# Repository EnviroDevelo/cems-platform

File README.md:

# CEMS Core Platform firmware

Shared firmware platform for the CEMS Supervisor instrument family (STM32H5, FreeRTOS,
lwIP, Riverdi EVE4). It runs the translated Valve Manager / Multiplexor program as a
PLC-style scan and provides the services around it.

- `docs/APP_INTEGRATION.md`: handover for the VM/MUX application build (what to supply, rules, open items)
- `docs/PLATFORM.md`: structure, task priorities, the scan contract, integration rules, decisions needed
- `docs/CUBEMX_SETUP.md`: bringing it up on the STM32H573I-DK in STM32CubeIDE
- `docs/MEMORY.md`: flash and RAM used by each module against the chip's limits (kept current)

## Host builds (Linux/macOS/WSL, gcc)

```
make test      # unit tests (with both FRAM memory maps; includes 400 random power cuts on the log)
make sim       # PC simulation of the demo application
make netsim    # the platform on real sockets: Modbus TCP on 1502, web on https://127.0.0.1:8443/
               # (FRAM and log flash are files: netsim_fram.bin, netsim_nor.bin)
               # (type "remote" / "local" on stdin to act as the touchscreen)
make rtos      # the real FreeRTOS task layer on the FreeRTOS POSIX port (needs EXT=path with FreeRTOS-Kernel)
make target    # compile-check for STM32H5 with arm-none-eabi-gcc (needs EXT, see port/stm32h5/check.mk)
tools/check_target.sh   # compile and link the target in six configurations; updates docs/MEMORY.md
```

Integration tests (with netsim built): `python3 tests/integration/net_test.py` (needs
pymodbus on PYTHONPATH), `python3 tests/integration/fw_test.py` (firmware update and
rollback), `python3 tests/integration/mail_test.py` (alarm email against a test mail
server; needs openssl), `python3 tests/integration/clock_test.py` (clock and SNTP), `python3 tests/integration/serial_test.py` (serial number tokens; needs Python cryptography),
`python3 tests/integration/soak_test.py [minutes]` (soak with memory and socket watch; needs pymodbus) and `python3 tests/integration/web_ui_test.py` (needs Python Playwright and
Chromium).

The application contract (`plat_app_t`) now includes `fw_safe` (may a firmware restart
happen now?) and `alarms`; see `app_demo/`.

Firmware update files: `tools/mkfwimage.py build.bin cems-x.y.z.cfw --version x.y.z`
(add `--key <pem>` to sign; key set-up in `docs/CUBEMX_SETUP.md` 3d).

Touchscreen previews: `UI_DUMP=build/ui ./build/tests` writes each screen's EVE command
list, and `python3 tools/eve_preview.py build/ui/*.eve` renders them to PNG (needs
Pillow). Current screens: `docs/ui/`.

The product build is the STM32CubeIDE project. These host builds are for testing
outside the IDE.
Third-party licences: `docs/THIRD_PARTY.md`. Schematic list and bring-up checks: `docs/HARDWARE.md`.
Screen colours, states, quality marks and wording for every product: `docs/UI_CONVENTIONS.md`.
First run of the touchscreen on hardware, step by step: `docs/HMI_BENCH_TEST.md` (System > Display test on the screen).
Operator manual for the touchscreen: `docs/OPERATOR_MANUAL.md`.

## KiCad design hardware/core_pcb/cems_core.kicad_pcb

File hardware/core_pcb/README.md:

# Core PCB (KiCad 7)

The CEMS core board schematic, rev 0.1 (draft for review). Design spec, pin map and
decisions: [`docs/CORE_PCB.md`](../../docs/CORE_PCB.md).

| File | What |
|---|---|
| `cems_core.pdf` | All sheets, for review without KiCad |
| `cems_core.kicad_pro`, `cems_core.kicad_sch` | KiCad project and root sheet |
| `power`, `mcu`, `eth_client`, `eth_io`, `periph`, `io_dig`, `io_pwr`, `io_ana` `.kicad_sch` | The eight sheets (rev 0.2: 434 parts, 314 nets) |
| `cems_core.kicad_sym`, `sym-lib-table` | Project symbols (the MB85RC1MT FRAM) |
| `bom.csv` | Grouped bill of materials |
| `tools/design.py` | **The circuit, as data: edit this, not the sheets** |
| `tools/gen_schematic.py` | Writes the sheets and `bom.csv` from `design.py` |
| `cems_core.kicad_pcb`, `cems_core.kicad_dru`, `cems_core.pretty/` | Layout start (block plan, unrouted), isolation rules, project footprints. CORE_PCB.md 10a |
| `tools/gen_pcb.py`, `tools/gen_footprints.py` | Write the board and the project footprints from `design.py` |
| `tools/project_symbols.py` | Pin tables of the six I/O chips missing from KiCad (all CHECK) |
| `tools/check_netlist.py` | Checks KiCad's exported netlist against `design.py`, pin by pin |
| `tools/build.sh` | Runs all three and exports the PDF |

Needs KiCad 7 (`kicad-cli` and its symbol libraries; Ubuntu: `apt install kicad
kicad-symbols kicad-footprints`) and `pip install kiutils`. Footprints are the KiCad 7
library names, so the netlist imports straight into Pcbnew for layout.

Once layout starts, the schematic may be tidied by hand in KiCad (wires in place of
labels). From then on it is the source, and `design.py` is kept only as a record.

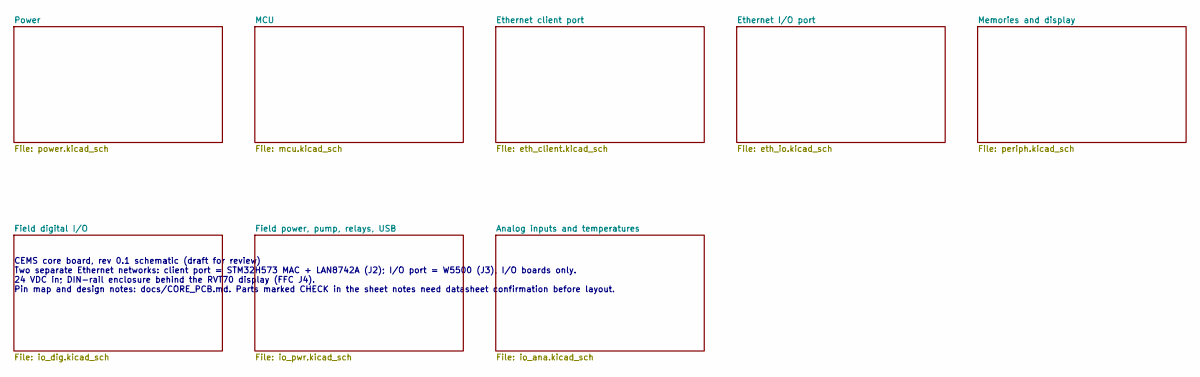
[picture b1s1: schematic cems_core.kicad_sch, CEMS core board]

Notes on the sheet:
CEMS core board, rev 0.1 schematic (draft for review) Two separate Ethernet networks: client port = STM32H573 MAC + LAN8742A (J2); I/O port = W5500 (J3), I/O boards only. 24 VDC in; DIN-rail enclosure behind the RVT70 display (FFC J4). Pin map and design notes: docs/CORE_PCB.md. Parts marked CHECK 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

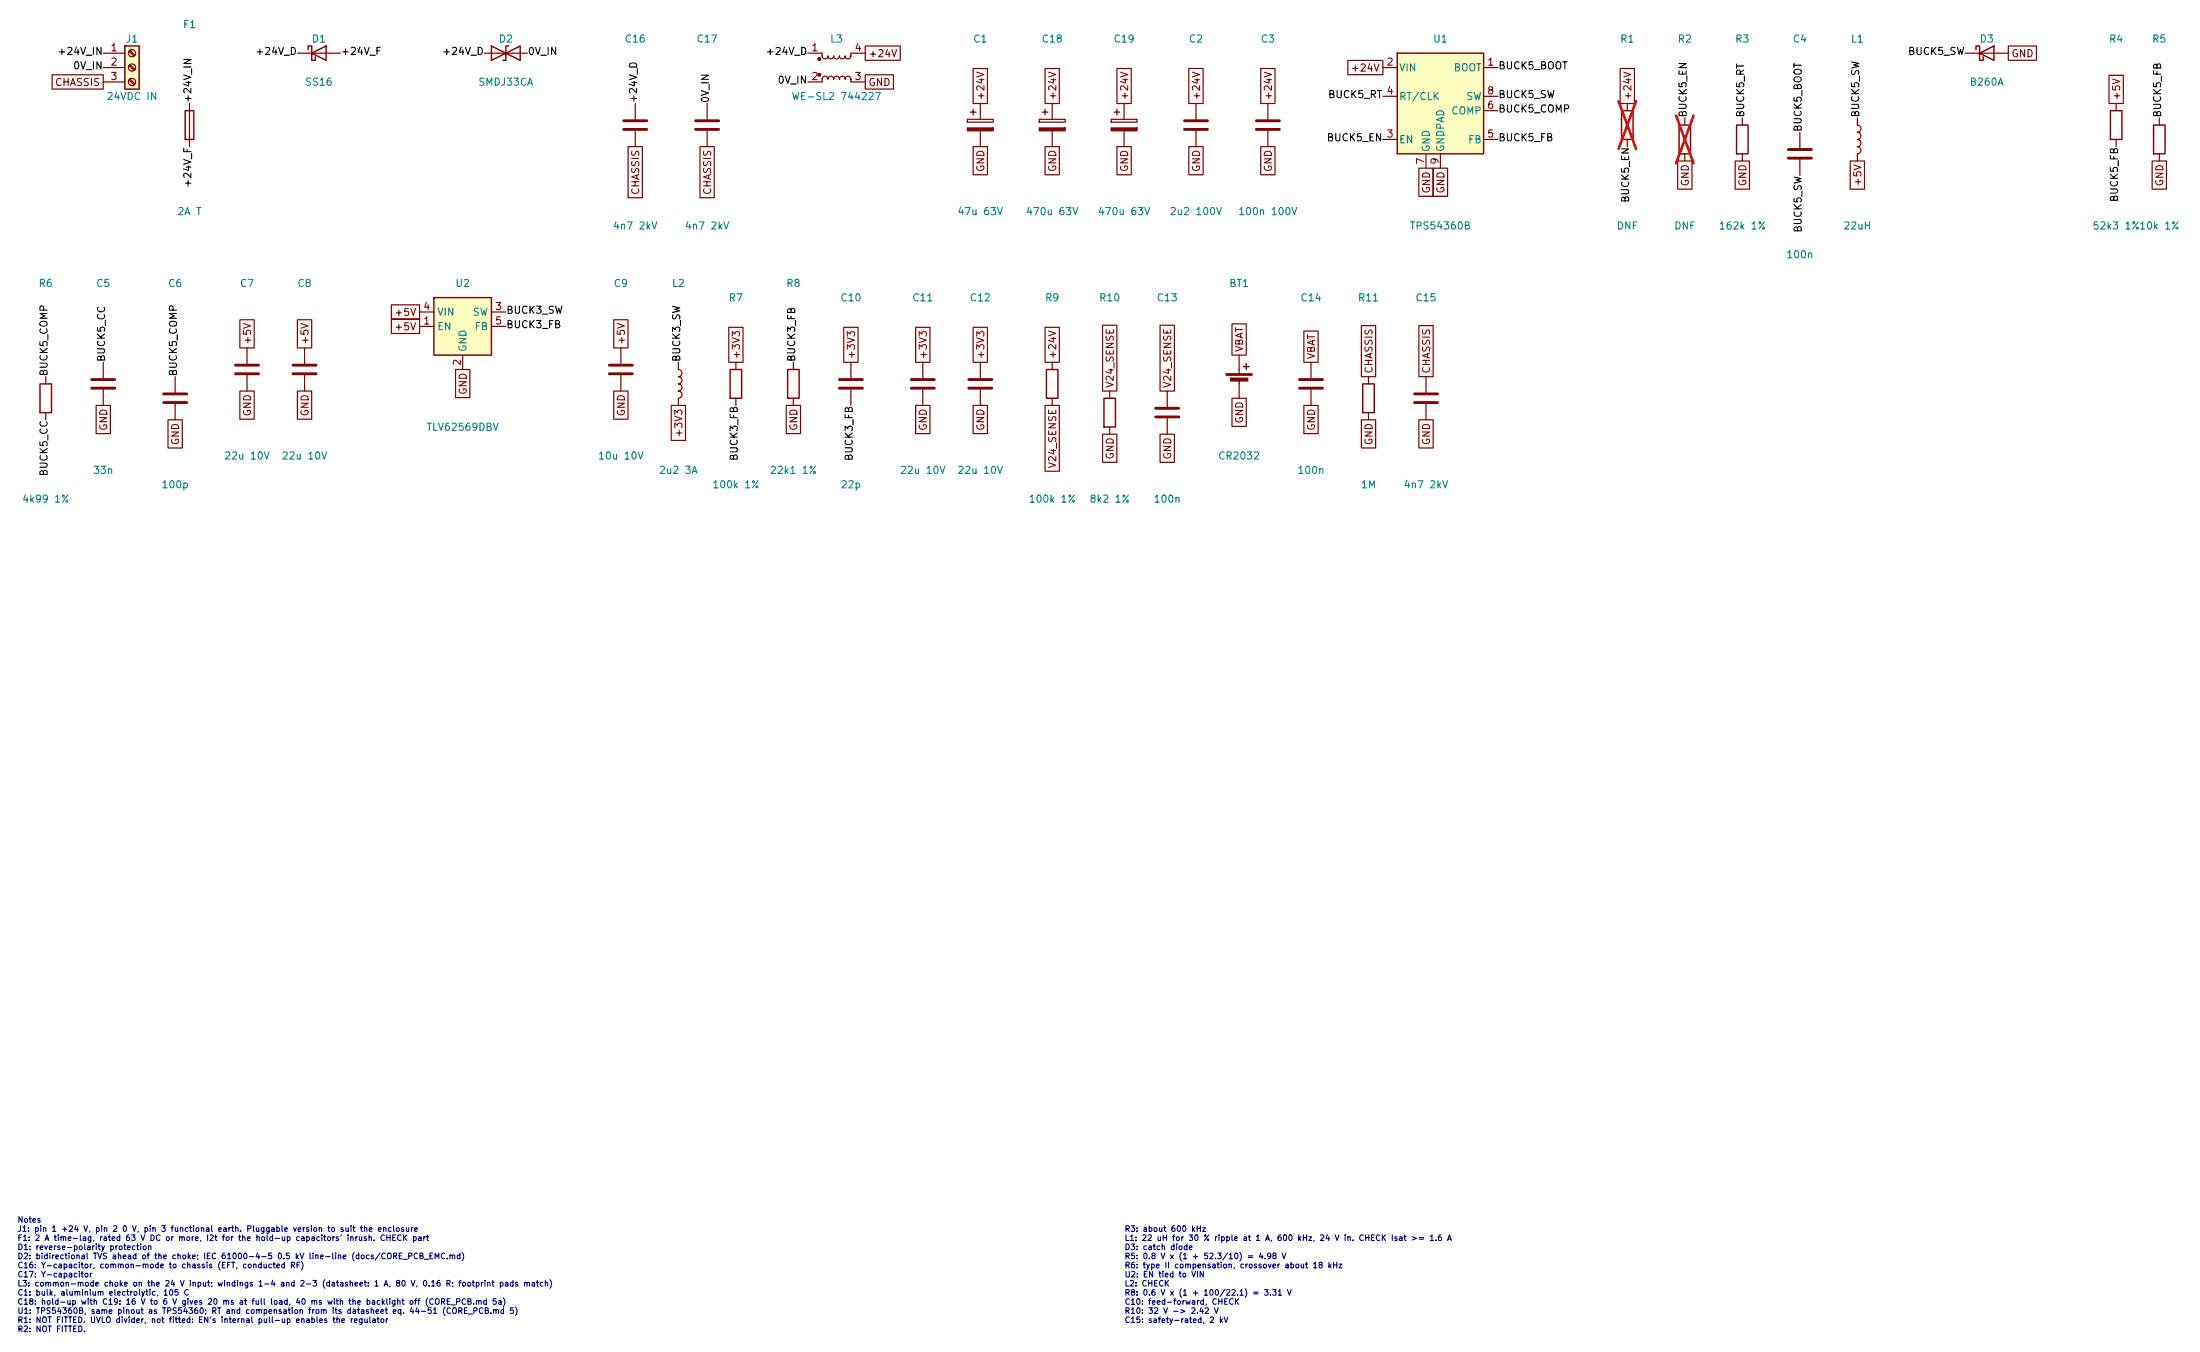
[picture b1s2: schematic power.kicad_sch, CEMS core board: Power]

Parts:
BT1: CR2032; BatteryHolder_Keystone_3034_1x20mm; MPN Keystone 3034 holder + CR2032
C1: 47u 63V; CP_Elec_8x10; MPN 47u 63V
C2: 2u2 100V; C_1210_3225Metric; MPN 2u2 100V
C3: 100n 100V; C_0603_1608Metric; MPN 100n 100V
C4, C13, C14: 100n; C_0603_1608Metric; MPN 100n
C5: 33n; C_0603_1608Metric; MPN 33n
C6: 100p; C_0603_1608Metric; MPN 100p
C7, C8: 22u 10V; C_1210_3225Metric; MPN 22u 10V
C9: 10u 10V; C_0805_2012Metric; MPN 10u 10V
C10: 22p; C_0603_1608Metric; MPN 22p
C11, C12: 22u 10V; C_1206_3216Metric; MPN 22u 10V
C15, C16, C17: 4n7 2kV; C_1812_4532Metric; MPN 4n7 2kV
C18, C19: 470u 63V; CP_Radial_D12.5mm_P5.00mm; MPN 470 uF 63 V, 105 C, low ESR, 12.5 mm ra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
D1: SS16; D_SMA; MPN SS16 (60 V, 1 A)
D2: SMDJ33CA; D_SMC; MPN SMDJ33CA (3 kW)
D3: B260A; D_SMA; MPN B260A-13 (60 V, 2 A)
F1: 2A T; Fuse_1206_3216Metric; MPN 2A T
J1: 24VDC IN; TerminalBlock_Phoenix_MKDS-1,5-3-5.08_1x03_P5.08mm_Horizont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; MPN 24VDC IN
L1: 22uH; L_Bourns_SRN6045TA; MPN Bourns SRN6045TA-220M
L2: 2u2 3A; L_Wuerth_MAPI-4030; MPN Wurth 74438357022 (MAPI 4030, 2.2 uH)
L3: WE-SL2 744227; L_CommonMode_Wuerth_WE-SL2; MPN Wurth 744227
R1, R2: DNF; R_0603_1608Metric; MPN DNF; not fitted
R3: 162k 1%; R_0603_1608Metric; MPN 162k 1%
R4: 52k3 1%; R_0603_1608Metric; MPN 52k3 1%
R5: 10k 1%; R_0603_1608Metric; MPN 10k 1%
R6: 4k99 1%; R_0603_1608Metric; MPN 4k99 1%
R7, R9: 100k 1%; R_0603_1608Metric; MPN 100k 1%
R8: 22k1 1%; R_0603_1608Metric; MPN 22k1 1%
R10: 8k2 1%; R_0603_1608Metric; MPN 8k2 1%
R11: 1M; R_1206_3216Metric; MPN 1M
U1: TPS54360B; TI_SO-PowerPAD-8_ThermalVias; MPN TPS54360BDDAR
U2: TLV62569DBV; SOT-23-5; MPN TLV62569DBVR

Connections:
0V_IN: C17.1, D2.2 (A2), J1.2, L3.2
+3V3: C10.1, C11.1, C12.1, L2.2, R7.1; also elsewhere on the board
+5V: C7.1, C8.1, C9.1, L1.2, R4.1, U2.1 (EN), U2.4 (VIN); also elsewhere on the board
+24V: C1.1, C2.1, C3.1, C18.1, C19.1, L3.4, R1.1, R9.1, U1.2 (VIN); also elsewhere on the board
+24V_D: C16.1, D1.1 (K), D2.1 (A1), L3.1
+24V_F: D1.2 (A), F1.2
+24V_IN: F1.1, J1.1
BUCK3_FB: C10.2, R7.2, R8.1, U2.5 (FB)
BUCK3_SW: L2.1, U2.3 (SW)
BUCK5_BOOT: C4.1, U1.1 (BOOT)
BUCK5_CC: C5.1, R6.2
BUCK5_COMP: C6.1, R6.1, U1.6 (COMP)
BUCK5_EN: R1.2, R2.1, U1.3 (EN)
BUCK5_FB: R4.2, R5.1, U1.5 (FB)
BUCK5_RT: R3.1, U1.4 (RT/CLK)
BUCK5_SW: C4.2, D3.1 (K), L1.1, U1.8 (SW)
CHASSIS: C15.1, C16.2, C17.2, J1.3, R11.1; also elsewhere on the board
GND: BT1.2 (-), C1.2, C2.2, C3.2, C5.2, C6.2, C7.2, C8.2, C9.2, C11.2, C12.2, C13.2, C14.2, C15.2, C18.2, C19.2, D3.2 (A), L3.3, R2.2, R3.2, R5.2, R8.2, R10.2, R11.2, U1.7 (GND), U1.9 (GNDPAD), U2.2 (GND); also elsewhere on the board
V24_SENSE: C13.1, R9.2, R10.1; also elsewhere on the board
VBAT: BT1.1 (+), C14.1; also elsewhere on the board

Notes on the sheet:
Notes J1: pin 1 +24 V, pin 2 0 V, pin 3 functional earth. Pluggable version to suit the enclosure F1: 2 A time-lag, rated 63 V DC or more, I2t for the hold-up capacitors' inrush. CHECK part D1: reverse-polarity protection D2: bidirectional TVS ahead of the choke; IEC 61000-4-5 0.5 kV line-line (doc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
R3: about 600 kHz L1: 22 uH for 30 % ripple at 1 A, 600 kHz, 24 V in. CHECK Isat >= 1.6 A D3: catch diode R5: 0.8 V x (1 + 52.3/10) = 4.98 V R6: type II compensation, crossover about 18 kHz U2: EN tied to VIN L2: CHECK R8: 0.6 V x (1 + 100/22.1) = 3.31 V C10: feed-forward, CHECK R10: 32 V -> 2.42 V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

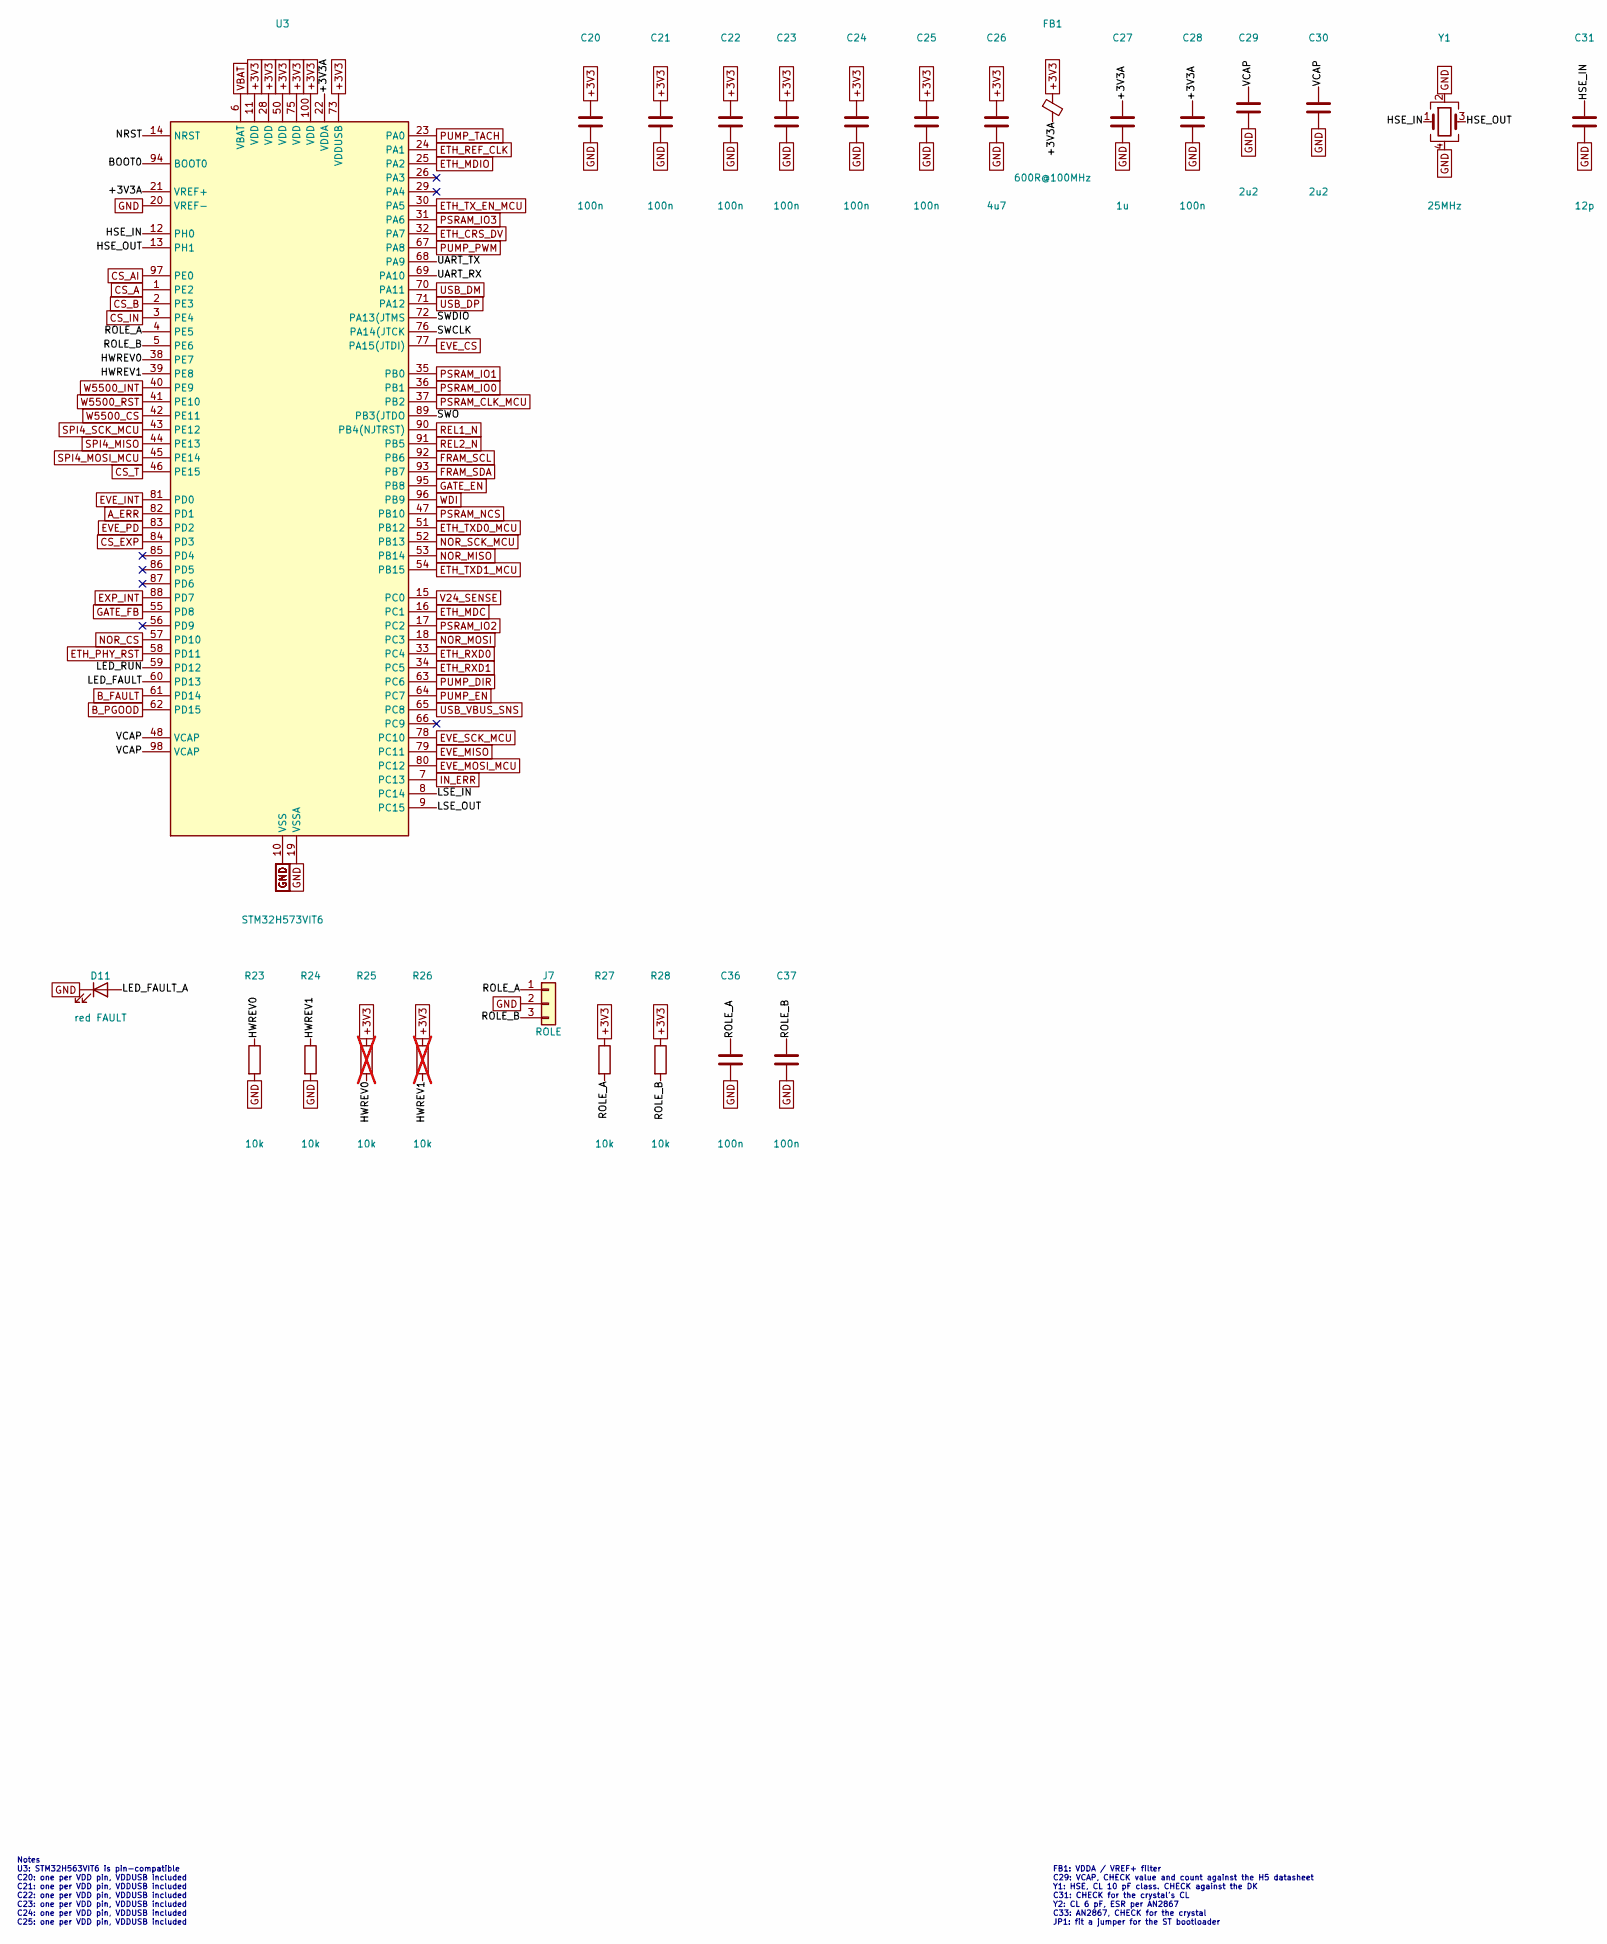
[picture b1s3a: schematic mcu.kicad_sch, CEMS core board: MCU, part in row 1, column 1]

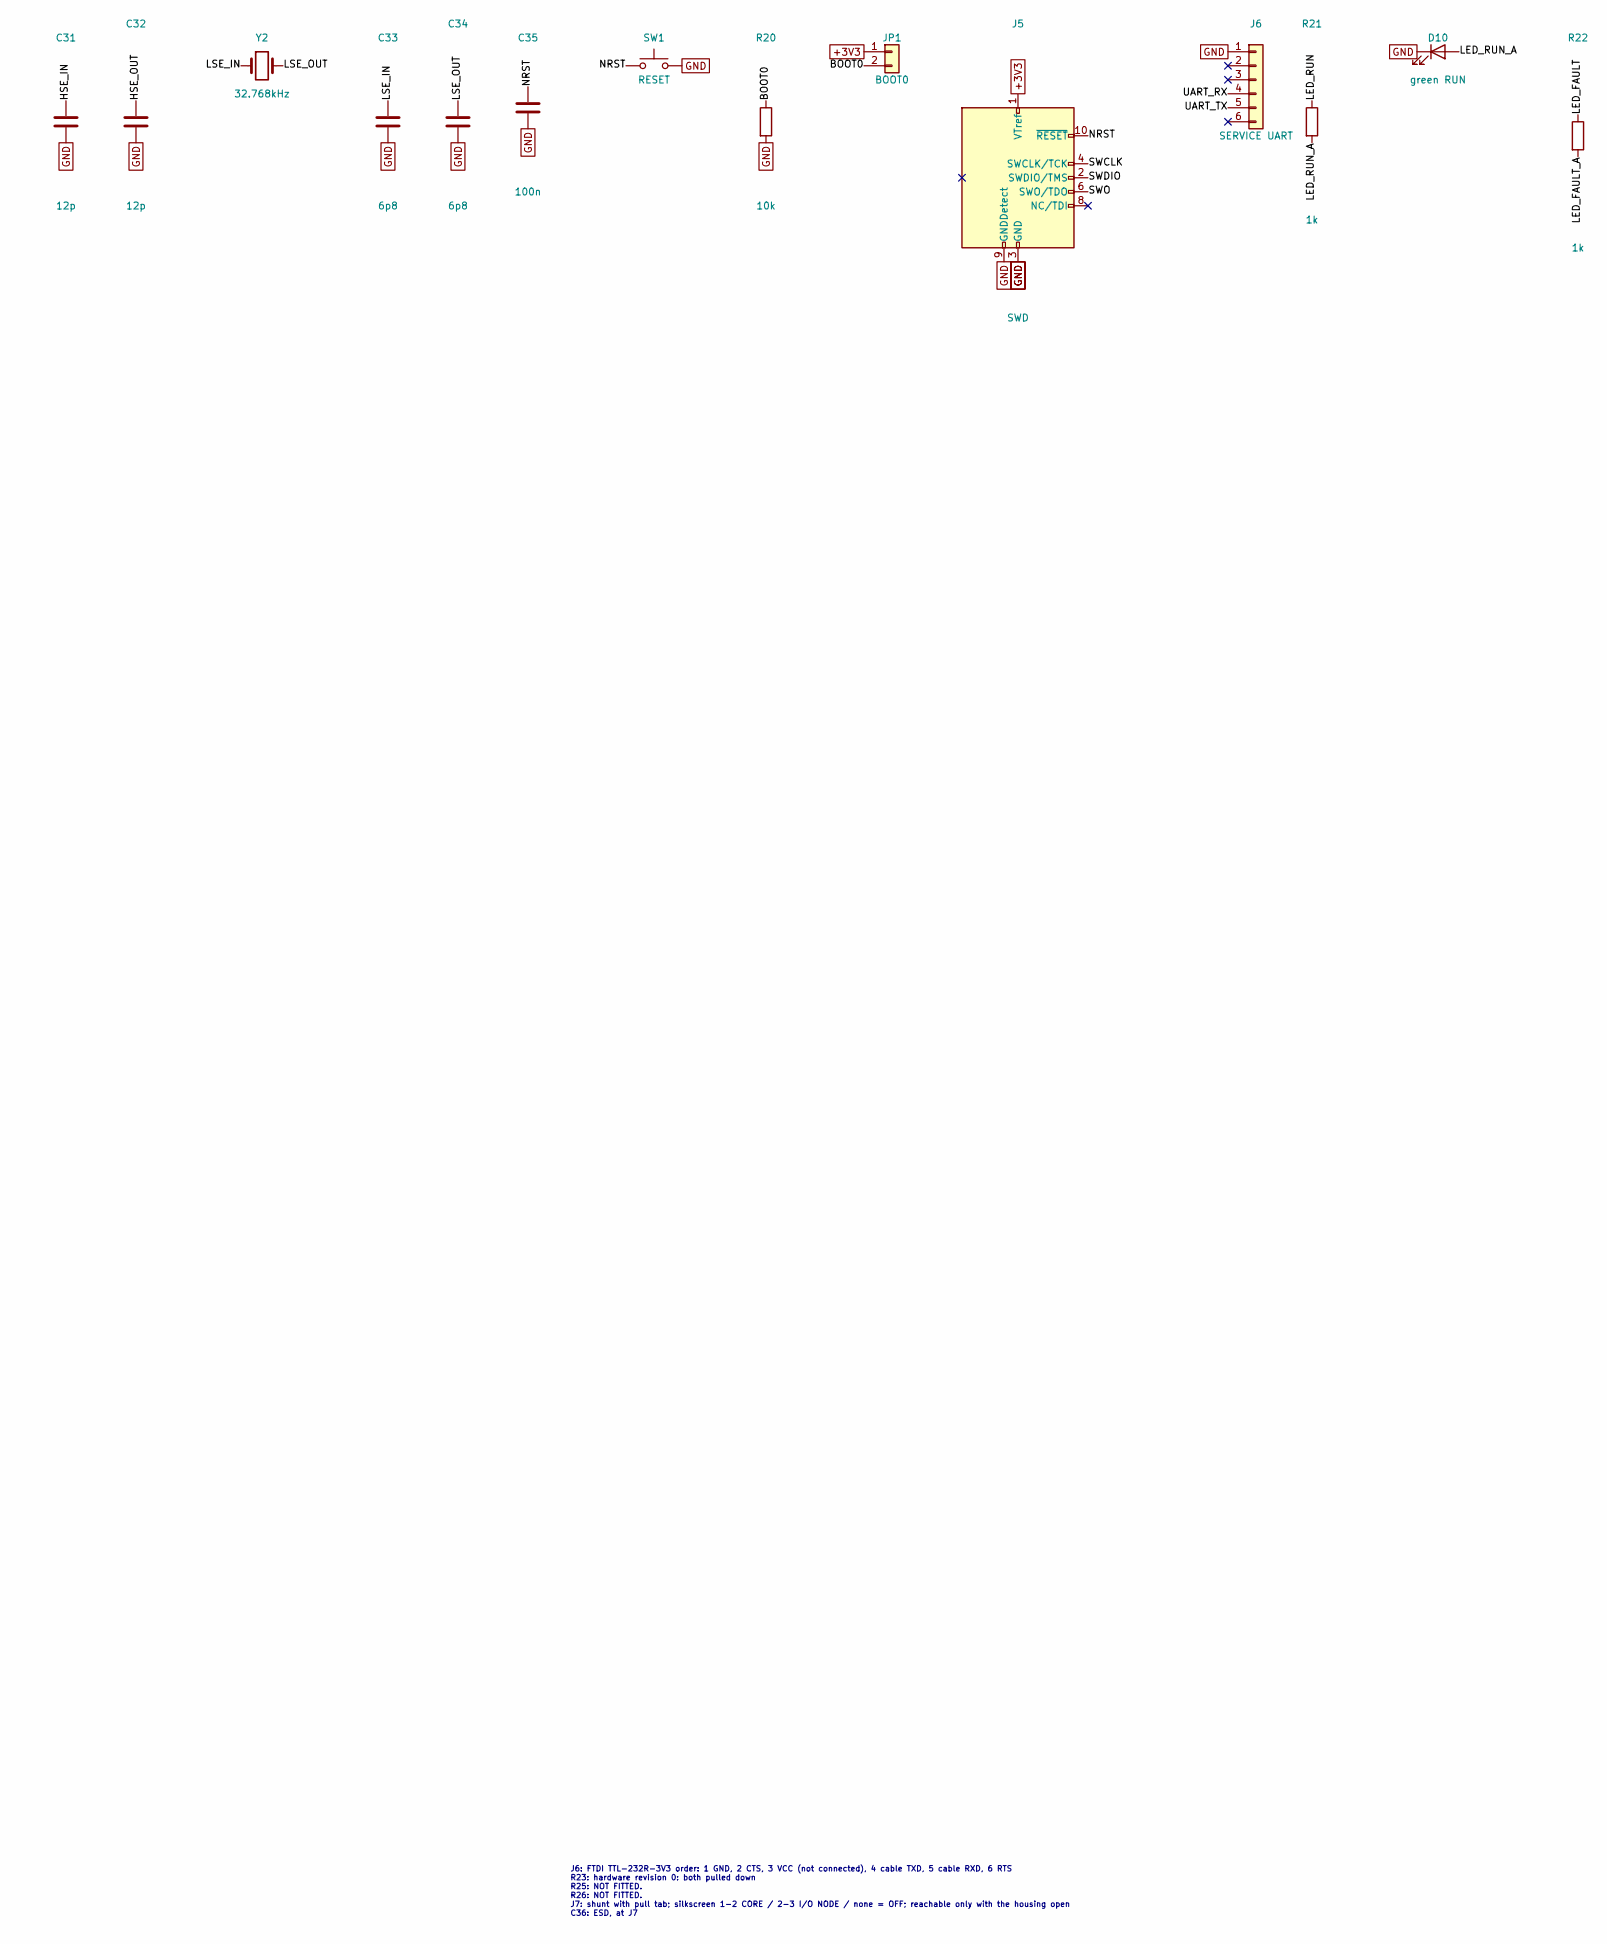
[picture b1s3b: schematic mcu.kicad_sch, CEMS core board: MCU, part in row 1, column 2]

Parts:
C20, C21, C22, C23, C24, C25, C28, C35, C36, C37: 100n; C_0603_1608Metric; MPN 100n
C26: 4u7; C_0805_2012Metric; MPN 4u7
C27: 1u; C_0603_1608Metric; MPN 1u
C29, C30: 2u2; C_0603_1608Metric; MPN 2u2
C31, C32: 12p; C_0603_1608Metric; MPN 12p
C33, C34: 6p8; C_0603_1608Metric; MPN 6p8
D10: green RUN; LED_0603_1608Metric; MPN green RUN
D11: red FAULT; LED_0603_1608Metric; MPN red FAULT
FB1: 600R@100MHz; L_0603_1608Metric; MPN 600R@100MHz
J5: SWD; PinHeader_2x05_P1.27mm_Vertical_SMD; MPN SWD
J6: SERVICE UART; PinHeader_1x06_P2.54mm_Vertical; MPN SERVICE UART
J7: ROLE; PinHeader_1x03_P2.54mm_Vertical; MPN ROLE
JP1: BOOT0; PinHeader_1x02_P2.54mm_Vertical; MPN BOOT0
R20, R23, R24, R27, R28: 10k; R_0603_1608Metric; MPN 10k
R21, R22: 1k; R_0603_1608Metric; MPN 1k
R25, R26: 10k; R_0603_1608Metric; MPN 10k; not fitted
SW1: RESET; SW_SPST_B3U-1000P; MPN RESET
U3: STM32H573VIT6; LQFP-100_14x14mm_P0.5mm; MPN STM32H573VIT6
Y1: 25MHz; Crystal_SMD_3225-4Pin_3.2x2.5mm; MPN 25MHz
Y2: 32.768kHz; Crystal_SMD_3215-2Pin_3.2x1.5mm; MPN 32.768kHz

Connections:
+3V3: C20.1, C21.1, C22.1, C23.1, C24.1, C25.1, C26.1, FB1.1, J5.1 (VTref), JP1.1, R25.1, R26.1, R27.1, R28.1, U3.11 (VDD), U3.28 (VDD), U3.50 (VDD), U3.73 (VDDUSB), U3.75 (VDD), U3.100 (VDD); also elsewhere on the board
+3V3A: C27.1, C28.1, FB1.2, U3.21 (VREF+), U3.22 (VDDA)
A_ERR: U3.82 (PD1); also elsewhere on the board
BOOT0: JP1.2, R20.1, U3.94 (BOOT0)
B_FAULT: U3.61 (PD14); also elsewhere on the board
B_PGOOD: U3.62 (PD15); also elsewhere on the board
CS_A: U3.1 (PE2); also elsewhere on the board
CS_AI: U3.97 (PE0); also elsewhere on the board
CS_B: U3.2 (PE3); also elsewhere on the board
CS_EXP: U3.84 (PD3); also elsewhere on the board
CS_IN: U3.3 (PE4); also elsewhere on the board
CS_T: U3.46 (PE15); also elsewhere on the board
ETH_CRS_DV: U3.32 (PA7); also elsewhere on the board
ETH_MDC: U3.16 (PC1); also elsewhere on the board
ETH_MDIO: U3.25 (PA2); also elsewhere on the board
ETH_PHY_RST: U3.58 (PD11); also elsewhere on the board
ETH_REF_CLK: U3.24 (PA1); also elsewhere on the board
ETH_RXD0: U3.33 (PC4); also elsewhere on the board
ETH_RXD1: U3.34 (PC5); also elsewhere on the board
ETH_TXD0_MCU: U3.51 (PB12); also elsewhere on the board
ETH_TXD1_MCU: U3.54 (PB15); also elsewhere on the board
ETH_TX_EN_MCU: U3.30 (PA5); also elsewhere on the board
EVE_CS: U3.77 (PA15(JTDI)); also elsewhere on the board
EVE_INT: U3.81 (PD0); also elsewhere on the board
EVE_MISO: U3.79 (PC11); also elsewhere on the board
EVE_MOSI_MCU: U3.80 (PC12); also elsewhere on the board
EVE_PD: U3.83 (PD2); also elsewhere on the board
EVE_SCK_MCU: U3.78 (PC10); also elsewhere on the board
EXP_INT: U3.88 (PD7); also elsewhere on the board
FRAM_SCL: U3.92 (PB6); also elsewhere on the board
FRAM_SDA: U3.93 (PB7); also elsewhere on the board
GATE_EN: U3.95 (PB8); also elsewhere on the board
GATE_FB: U3.55 (PD8); also elsewhere on the board
GND: C20.2, C21.2, C22.2, C23.2, C24.2, C25.2, C26.2, C27.2, C28.2, C29.2, C30.2, C31.2, C32.2, C33.2, C34.2, C35.2, C36.2, C37.2, D10.1 (K), D11.1 (K), J5.3 (GND), J5.5 (GND), J5.9 (GNDDetect), J6.1, J7.2, R20.2, R23.2, R24.2, SW1.2, U3.10 (VSS), U3.19 (VSSA), U3.20 (VREF-), U3.27 (VSS), U3.49 (VSS), U3.74 (VSS), U3.99 (VSS), Y1.2, Y1.4; also elsewhere on the board
HSE_IN: C31.1, U3.12 (PH0), Y1.1
HSE_OUT: C32.1, U3.13 (PH1), Y1.3
HWREV0: R23.1, R25.2, U3.38 (PE7)
HWREV1: R24.1, R26.2, U3.39 (PE8)
IN_ERR: U3.7 (PC13); also elsewhere on the board
LED_FAULT: R22.1, U3.60 (PD13)
LED_FAULT_A: D11.2 (A), R22.2
LED_RUN: R21.1, U3.59 (PD12)
LED_RUN_A: D10.2 (A), R21.2
LSE_IN: C33.1, U3.8 (PC14), Y2.1
LSE_OUT: C34.1, U3.9 (PC15), Y2.2
NOR_CS: U3.57 (PD10); also elsewhere on the board
NOR_MISO: U3.53 (PB14); also elsewhere on the board
NOR_MOSI: U3.18 (PC3); also elsewhere on the board
NOR_SCK_MCU: U3.52 (PB13); also elsewhere on the board
NRST: C35.1, J5.10 (~RESET), SW1.1, U3.14 (NRST)
PSRAM_CLK_MCU: U3.37 (PB2); also elsewhere on the board
PSRAM_IO0: U3.36 (PB1); also elsewhere on the board
PSRAM_IO1: U3.35 (PB0); also elsewhere on the board
PSRAM_IO2: U3.17 (PC2); also elsewhere on the board
PSRAM_IO3: U3.31 (PA6); also elsewhere on the board
PSRAM_NCS: U3.47 (PB10); also elsewhere on the board
PUMP_DIR: U3.63 (PC6); also elsewhere on the board
PUMP_EN: U3.64 (PC7); also elsewhere on the board
PUMP_PWM: U3.67 (PA8); also elsewhere on the board
PUMP_TACH: U3.23 (PA0); also elsewhere on the board
REL1_N: U3.90 (PB4(NJTRST)); also elsewhere on the board
REL2_N: U3.91 (PB5); also elsewhere on the board
ROLE_A: C36.1, J7.1, R27.2, U3.4 (PE5)
ROLE_B: C37.1, J7.3, R28.2, U3.5 (PE6)
SPI4_MISO: U3.44 (PE13); also elsewhere on the board
SPI4_MOSI_MCU: U3.45 (PE14); also elsewhere on the board
SPI4_SCK_MCU: U3.43 (PE12); also elsewhere on the board
SWCLK: J5.4 (SWCLK/TCK), U3.76 (PA14(JTCK)
SWDIO: J5.2 (SWDIO/TMS), U3.72 (PA13(JTMS)
SWO: J5.6 (SWO/TDO), U3.89 (PB3(JTDO)
UART_RX: J6.4, U3.69 (PA10)
UART_TX: J6.5, U3.68 (PA9)
USB_DM: U3.70 (PA11); also elsewhere on the board
USB_DP: U3.71 (PA12); also elsewhere on the board
USB_VBUS_SNS: U3.65 (PC8); also elsewhere on the board
V24_SENSE: U3.15 (PC0); also elsewhere on the board
VBAT: U3.6 (VBAT); also elsewhere on the board
VCAP: C29.1, C30.1, U3.48 (VCAP), U3.98 (VCAP)
W5500_CS: U3.42 (PE11); also elsewhere on the board
W5500_INT: U3.40 (PE9); also elsewhere on the board
W5500_RST: U3.41 (PE10); also elsewhere on the board
WDI: U3.96 (PB9); also elsewhere on the board

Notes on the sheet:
Notes U3: STM32H563VIT6 is pin-compatible C20: one per VDD pin, VDDUSB included C21: one per VDD pin, VDDUSB included C22: one per VDD pin, VDDUSB included C23: one per VDD pin, VDDUSB included C24: one per VDD pin, VDDUSB included C25: one per VDD pin, VDDUSB included
FB1: VDDA / VREF+ filter C29: VCAP, CHECK value and count against the H5 datasheet Y1: HSE, CL 10 pF class. CHECK against the DK C31: CHECK for the crystal's CL Y2: CL 6 pF, ESR per AN2867 C33: AN2867, CHECK for the crystal JP1: fit a jumper for the ST bootloader
J6: FTDI TTL-232R-3V3 order: 1 GND, 2 CTS, 3 VCC (not connected), 4 cable TXD, 5 cable RXD, 6 RTS R23: hardware revision 0: both pulled down R25: NOT FITTED. R26: NOT FITTED. J7: shunt with pull tab; silkscreen 1-2 CORE / 2-3 I/O NODE / none = OFF; reachable only with the housing open C36: ESD, at 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

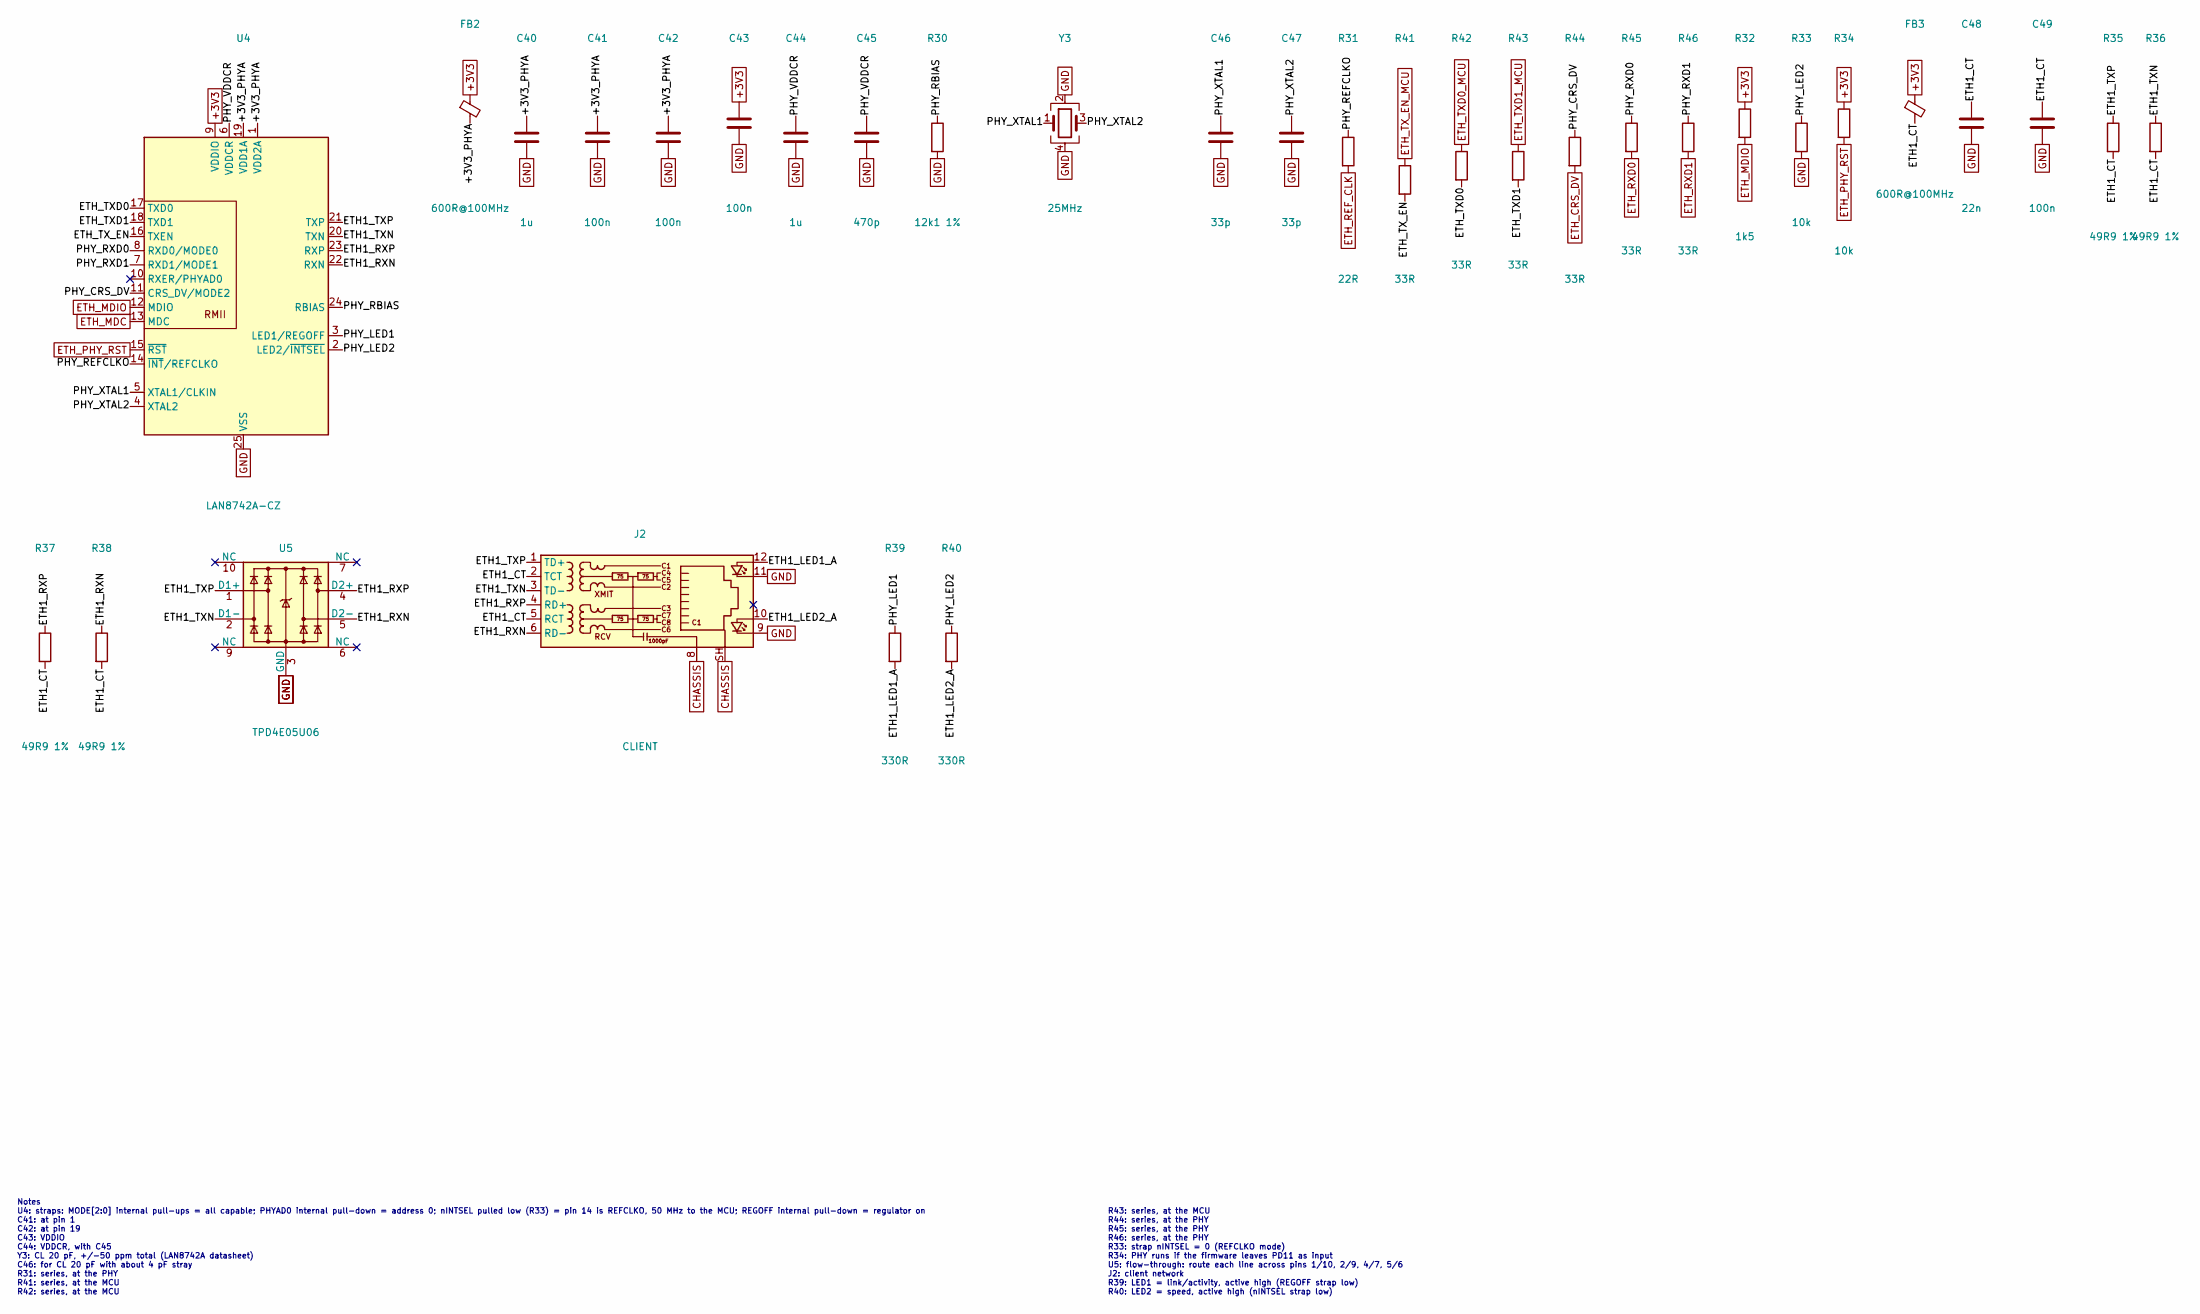
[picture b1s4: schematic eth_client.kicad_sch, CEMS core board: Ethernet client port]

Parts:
C40, C44: 1u; C_0603_1608Metric; MPN 1u
C41, C42, C43, C49: 100n; C_0603_1608Metric; MPN 100n
C45: 470p; C_0603_1608Metric; MPN 470p
C46, C47: 33p; C_0603_1608Metric; MPN 33p
C48: 22n; C_0603_1608Metric; MPN 22n
FB2, FB3: 600R@100MHz; L_0603_1608Metric; MPN 600R@100MHz
J2: CLIENT; RJ45_Wuerth_7499010121A_Horizontal; MPN Wurth 7499010121A (MagJack, 1500 Vrms, 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
R30: 12k1 1%; R_0603_1608Metric; MPN 12k1 1%
R31: 22R; R_0603_1608Metric; MPN 22R
R32: 1k5; R_0603_1608Metric; MPN 1k5
R33, R34: 10k; R_0603_1608Metric; MPN 10k
R35, R36, R37, R38: 49R9 1%; R_0603_1608Metric; MPN 49R9 1%
R39, R40: 330R; R_0603_1608Metric; MPN 330R
R41, R42, R43, R44, R45, R46: 33R; R_0603_1608Metric; MPN 33R
U4: LAN8742A-CZ; VQFN-24-1EP_4x4mm_P0.5mm_EP2.5x2.5mm_ThermalVias; MPN LAN8742A-CZ-TR (-40 to 85 C)
U5: TPD4E05U06; USON-10_2.5x1.0mm_P0.5mm; MPN TPD4E05U06
Y3: 25MHz; Crystal_SMD_3225-4Pin_3.2x2.5mm; MPN 25MHz

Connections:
+3V3: C43.1, FB2.1, FB3.1, R32.1, R34.1, U4.9 (VDDIO); also elsewhere on the board
+3V3_PHYA: C40.1, C41.1, C42.1, FB2.2, U4.1 (VDD2A), U4.19 (VDD1A)
CHASSIS: J2.8, J2.SH; also elsewhere on the board
ETH1_CT: C48.1, C49.1, FB3.2, J2.2 (TCT), J2.5 (RCT), R35.2, R36.2, R37.2, R38.2
ETH1_LED1_A: J2.12, R39.2
ETH1_LED2_A: J2.10, R40.2
ETH1_RXN: J2.6 (RD-), R38.1, U4.22 (RXN), U5.5 (D2-)
ETH1_RXP: J2.4 (RD+), R37.1, U4.23 (RXP), U5.4 (D2+)
ETH1_TXN: J2.3 (TD-), R36.1, U4.20 (TXN), U5.2 (D1-)
ETH1_TXP: J2.1 (TD+), R35.1, U4.21 (TXP), U5.1 (D1+)
ETH_CRS_DV: R44.2; also elsewhere on the board
ETH_MDC: U4.13 (MDC); also elsewhere on the board
ETH_MDIO: R32.2, U4.12 (MDIO); also elsewhere on the board
ETH_PHY_RST: R34.2, U4.15 (~RST); also elsewhere on the board
ETH_REF_CLK: R31.2; also elsewhere on the board
ETH_RXD0: R45.2; also elsewhere on the board
ETH_RXD1: R46.2; also elsewhere on the board
ETH_TXD0: R42.2, U4.17 (TXD0)
ETH_TXD0_MCU: R42.1; also elsewhere on the board
ETH_TXD1: R43.2, U4.18 (TXD1)
ETH_TXD1_MCU: R43.1; also elsewhere on the board
ETH_TX_EN: R41.2, U4.16 (TXEN)
ETH_TX_EN_MCU: R41.1; also elsewhere on the board
GND: C40.2, C41.2, C42.2, C43.2, C44.2, C45.2, C46.2, C47.2, C48.2, C49.2, J2.9, J2.11, R30.2, R33.2, U4.25 (VSS), U5.3 (GND), U5.8 (GND), Y3.2, Y3.4; also elsewhere on the board
PHY_CRS_DV: R44.1, U4.11 (CRS_DV/MODE2)
PHY_LED1: R39.1, U4.3 (LED1/REGOFF)
PHY_LED2: R33.1, R40.1, U4.2 (LED2/~INTSEL)
PHY_RBIAS: R30.1, U4.24 (RBIAS)
PHY_REFCLKO: R31.1, U4.14 (~INT/REFCLKO)
PHY_RXD0: R45.1, U4.8 (RXD0/MODE0)
PHY_RXD1: R46.1, U4.7 (RXD1/MODE1)
PHY_VDDCR: C44.1, C45.1, U4.6 (VDDCR)
PHY_XTAL1: C46.1, U4.5 (XTAL1/CLKIN), Y3.1
PHY_XTAL2: C47.1, U4.4 (XTAL2), Y3.3

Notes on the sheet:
Notes U4: straps: MODE[2:0] internal pull-ups = all capable; PHYAD0 internal pull-down = address 0; nINTSEL pulled low (R33) = pin 14 is REFCLKO, 50 MHz to the MCU; REGOFF internal pull-down = regulator on C41: at pin 1 C42: at pin 19 C43: VDDIO C44: VDDCR, with C45 Y3: CL 20 pF, +/-50 ppm total (L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
R43: series, at the MCU R44: series, at the PHY R45: series, at the PHY R46: series, at the PHY R33: strap nINTSEL = 0 (REFCLKO mode) R34: PHY runs if the firmware leaves PD11 as input U5: flow-through: route each line across pins 1/10, 2/9, 4/7, 5/6 J2: client network R39: LED1 = link/activity, ac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
